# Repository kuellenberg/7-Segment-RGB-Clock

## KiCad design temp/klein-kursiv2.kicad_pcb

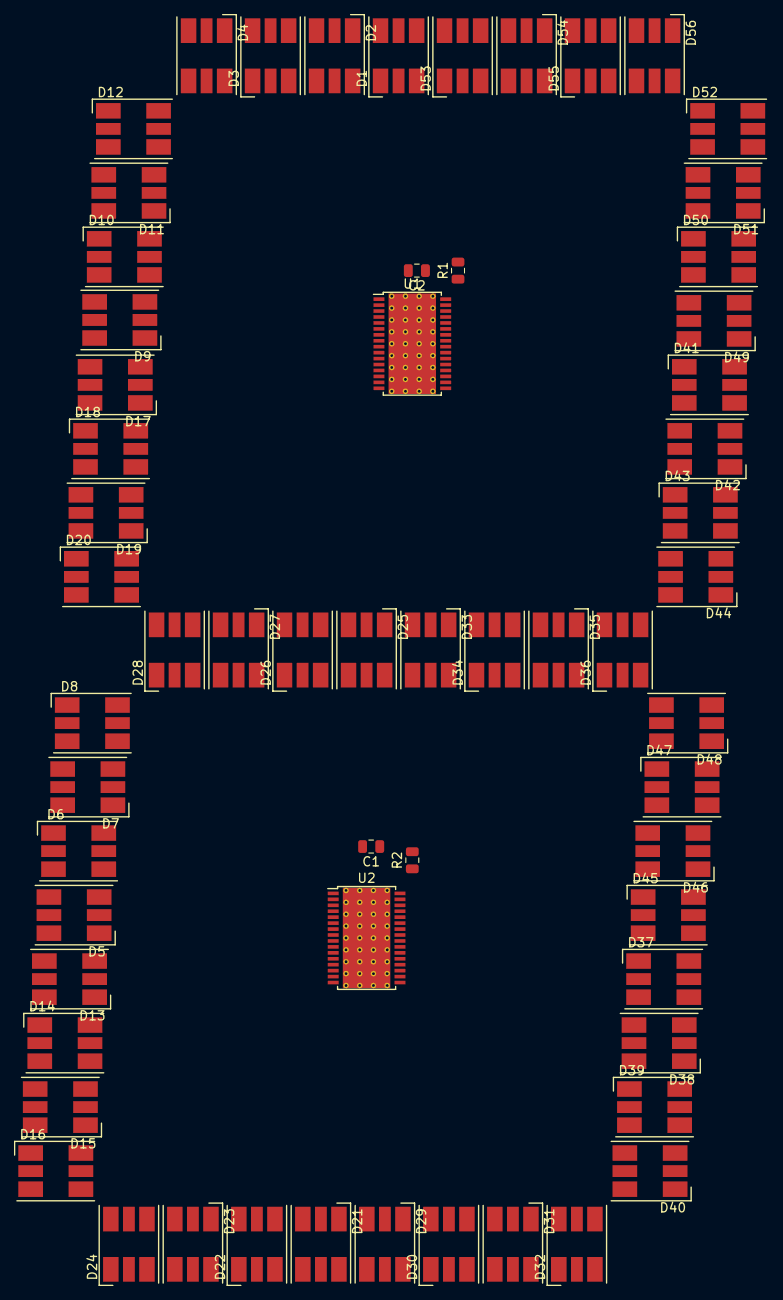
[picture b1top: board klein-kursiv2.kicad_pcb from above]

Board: 2 copper layers, 62 parts (0 on the bottom side), 177 nets, no tracks yet.

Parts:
C1, C2: C_Small; C_0805_2012Metric
D1, D2, D3, D4, D5, D6, D7, D8, D9, D10, D11, D12, D13, D14, D15, D16, D17, D18, D19, D20, D21, D22, D23, D24, D25, D26, D27, D28, D29, D30, D31, D32, D33, D34, D35, D36, D37, D38, D39, D40, D41, D42, D43, D44, D45, D46, D47, D48, D49, D50, D51, D52, D53, D54, D55, D56: LED_RGB; CREE_PLCC6_5.5x5.5
R1, R2: R_Small; R_0805_2012Metric
U1, U2: TLC5952; HTSSOP-32-1EP_6.1x11mm_P0.65mm_EP5.2x11mm_Mask4.11x4.36mm_T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

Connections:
GND: C1.2, C2.2, R1.2, R2.2, U1.1, U2.1
unnamed: D1.1, U1.7
unnamed: D1.2, U1.6
unnamed: D1.3, U1.5
unnamed: D1.4, D2.3
unnamed: D1.5, D2.2
unnamed: D1.6, D2.1
unnamed: D2.4, D3.3
unnamed: D2.5, D3.2
unnamed: D2.6, D3.1
unnamed: D3.4, D4.3
unnamed: D3.5, D4.2
unnamed: D3.6, D4.1
unnamed: D5.1, U2.7
unnamed: D5.2, U2.6
unnamed: D5.3, U2.5
unnamed: D5.4, D6.3
unnamed: D5.5, D6.2
unnamed: D5.6, D6.1
unnamed: D6.4, D7.3
unnamed: D6.5, D7.2
unnamed: D6.6, D7.1
unnamed: D7.4, D8.3
unnamed: D7.5, D8.2
unnamed: D7.6, D8.1
unnamed: D9.1, U1.10
unnamed: D9.2, U1.9
unnamed: D9.3, U1.8
unnamed: D9.6, D10.1
unnamed: D9.5, D10.2
unnamed: D9.4, D10.3
unnamed: D10.4, D11.3
unnamed: D10.5, D11.2
unnamed: D10.6, D11.1
unnamed: D11.4, D12.3
unnamed: D11.5, D12.2
unnamed: D11.6, D12.1
unnamed: D13.1, U2.10
unnamed: D13.2, U2.9
unnamed: D13.3, U2.8
unnamed: D13.4, D14.3
unnamed: D13.5, D14.2
unnamed: D13.6, D14.1
unnamed: D14.4, D15.3
unnamed: D14.5, D15.2
unnamed: D14.6, D15.1
unnamed: D15.4, D16.3
unnamed: D15.5, D16.2
unnamed: D15.6, D16.1
unnamed: D17.1, U1.13
unnamed: D17.2, U1.12
unnamed: D17.3, U1.11
unnamed: D17.4, D18.3
unnamed: D17.5, D18.2
unnamed: D17.6, D18.1
unnamed: D18.4, D19.3
unnamed: D18.5, D19.2
unnamed: D18.6, D19.1
unnamed: D19.4, D20.3
unnamed: D19.5, D20.2
unnamed: D19.6, D20.1
unnamed: D21.1, U2.13
unnamed: D21.2, U2.12
unnamed: D21.3, U2.11
unnamed: D21.4, D22.3
unnamed: D21.5, D22.2
unnamed: D21.6, D22.1
unnamed: D22.4, D23.3
unnamed: D22.5, D23.2
unnamed: D22.6, D23.1
unnamed: D23.4, D24.3
unnamed: D23.5, D24.2
unnamed: D23.6, D24.1
unnamed: D25.1, U1.16
unnamed: D25.2, U1.15
unnamed: D25.3, U1.14
unnamed: D25.4, D26.3
unnamed: D25.5, D26.2
unnamed: D25.6, D26.1
unnamed: D26.4, D27.3
unnamed: D26.5, D27.2
unnamed: D26.6, D27.1
unnamed: D27.4, D28.3
unnamed: D27.5, D28.2
unnamed: D27.6, D28.1
unnamed: D29.1, U2.16
unnamed: D29.2, U2.15
unnamed: D29.3, U2.14
unnamed: D29.4, D30.3
unnamed: D29.5, D30.2
unnamed: D29.6, D30.1
unnamed: D30.4, D31.3
unnamed: D30.5, D31.2
unnamed: D30.6, D31.1
unnamed: D31.4, D32.3
unnamed: D31.5, D32.2
unnamed: D31.6, D32.1
unnamed: D33.1, U1.19
unnamed: D33.2, U1.18
unnamed: D33.3, U1.17
unnamed: D33.4, D34.3
unnamed: D33.5, D34.2
unnamed: D33.6, D34.1
unnamed: D34.4, D35.3
unnamed: D34.5, D35.2
unnamed: D34.6, D35.1
unnamed: D35.4, D36.3
unnamed: D35.5, D36.2
unnamed: D35.6, D36.1
unnamed: D37.1, U2.19
unnamed: D37.2, U2.18
unnamed: D37.3, U2.17
unnamed: D37.4, D38.3
unnamed: D37.5, D38.2
unnamed: D37.6, D38.1
unnamed: D38.4, D39.3
unnamed: D38.5, D39.2
unnamed: D38.6, D39.1
unnamed: D39.4, D40.3
unnamed: D39.5, D40.2
unnamed: D39.6, D40.1
unnamed: D41.1, U1.22
unnamed: D41.2, U1.21
unnamed: D41.3, U1.20
unnamed: D41.4, D42.3
unnamed: D41.5, D42.2
unnamed: D41.6, D42.1
unnamed: D42.4, D43.3
unnamed: D42.5, D43.2
unnamed: D42.6, D43.1
unnamed: D43.4, D44.3
unnamed: D43.5, D44.2
unnamed: D43.6, D44.1
unnamed: D45.1, U2.22
unnamed: D45.2, U2.21
unnamed: D45.3, U2.20
unnamed: D45.4, D46.3
unnamed: D45.5, D46.2
unnamed: D45.6, D46.1
unnamed: D46.4, D47.3
unnamed: D46.5, D47.2
unnamed: D46.6, D47.1
unnamed: D47.4, D48.3
unnamed: D47.5, D48.2
unnamed: D47.6, D48.1
unnamed: D49.1, U1.25
unnamed: D49.2, U1.24
unnamed: D49.3, U1.23
unnamed: D49.4, D50.3
unnamed: D49.5, D50.2
unnamed: D49.6, D50.1
unnamed: D50.4, D51.3
unnamed: D50.5, D51.2
unnamed: D50.6, D51.1
unnamed: D51.4, D52.3
unnamed: D51.5, D52.2
unnamed: D51.6, D52.1
unnamed: D53.1, U1.28
unnamed: D53.2, U1.27
unnamed: D53.3, U1.26
unnamed: D53.4, D54.3
unnamed: D53.5, D54.2
unnamed: D53.6, D54.1
unnamed: D54.4, D55.3
unnamed: D54.5, D55.2
unnamed: D54.6, D55.1
unnamed: D55.4, D56.3
unnamed: D55.5, D56.2
unnamed: D55.6, D56.1
unnamed: U1.3, U2.3
unnamed: U1.4, U2.4
unnamed: U1.29, U2.29
unnamed: R1.1, U1.32
unnamed: R2.1, U2.32
unnamed: U1.30, U2.2
VCC: C1.1, C2.1, U1.31, U2.31
Vdrive: D4.4, D4.5, D4.6, D8.4, D8.5, D8.6, D12.4, D12.5, D12.6, D16.4, D16.5, D16.6, D20.4, D20.5, D20.6, D24.4, D24.5, D24.6, D28.4, D28.5, D28.6, D32.4, D32.5, D32.6, D36.4, D36.5, D36.6, D40.4, D40.5, D40.6, D44.4, D44.5, D44.6, D48.4, D48.5, D48.6, D52.4, D52.5, D52.6, D56.4, D56.5, D56.6
